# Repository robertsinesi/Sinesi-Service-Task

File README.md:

# KLM SRAM Expansion — Service Task

Belle II KLM service work · Instrumentation Development Lab, University of Hawai'i at Mānoa

## Overview

The KLM scintillator readout currently shares a single SRAM between the Bus A and
Bus B firmware modules through the SCROD FPGA. During multi-strip hits, pedestal
fetching becomes the rate-limiting step in waveform processing. This project adds
a second SRAM on an auxiliary daughtercard so each bus has its own memory path,
along with the power-distribution hardware needed to supply it.

Three boards make up the system:

| Board | Function |
| --- | --- |
| **Aux SRAM daughtercard** | Mounts to the spare 80-pin mezzanine connector on the scintillator motherboard; carries the second SRAM and a local 3.3 V regulator |
| **RTM +5 V board** | Rear transition module; taps +5 V from the crate backplane, fuses it, and feeds the wiring harness |
| **2-pole fanout board** | Splits the 12 AWG trunk into 22 AWG drops, one per SRAM card |

**Board design credit:** all three boards were designed by Chris Ketter (UH Mānoa),
with contributions from Horacio Ledesma. My role is prototype testing and design
finalization.

## Scope of this qualification task

Testing and validation:

- Test the prototype SRAM expansion board on the UH KLM testbench
- Test the associated RTM and power-distribution boards
- Verify electrical connections and power delivery across the full chain
- Confirm correct operation with the dedicated SRAM firmware

Finalization:

- Feed prototype results back into the board designs
- Help finalize assembly procedures ahead of the production run

Current files are in `Finalized-Boards/`. The SRAM card comes in three versions that share one outline and connector layout:

| Folder | Version |
| --- | --- |
| `KLM_aux_SRAM` | Standard card |
| `KLM_aux_SRAM_resistor` | Adds a 1 ohm current-sense resistor (R3) and two wire pads, so the supply current can be read with a meter (1 mV = 1 mA) |
| `KLM_aux_SRAM_INA226` | Standard card plus a 1 ohm current-sense resistor (R3, no wire pads) and an INA226 current monitor, read over I2C on spare lines 0 and 2 |

Editions of the boards are kept as git tags instead of folders. Each tag is the date of the edition followed by a short description:

| Tag | Edition |
| --- | --- |
| `2026-08-28-before-first-review` | Boards before the first design review |
| `2026-09-16-first-review-applied` | First review and its follow-up applied |
| `2026-09-17-polyswitch-1.1A` | Second review applied, with the lab-stock 1.1 A polyswitches |
| `2026-09-22-version-2` | Third review applied, polyswitches sized to the load; the boards built in October 2026 |
| `2026-10-20-old-board-folders` | Last commit that still had the `Old_Boards_Moved_<M-D-YY>/` folders, including the original boards as received |
| `2026-11-16-version-3` | Hand-soldering revision: longer pads, re-spaced wire pads and fuses, fanout mounting hole, three SRAM versions (current) |

To see an edition, pick its tag in the branch menu on GitHub and browse or download the files.

## Deliverable

- Finalized board designs
- Production of the boards
- Installation of the boards

## After the qualification task

Continued contribution to board production, testing, and installation as part of
ongoing KLM service work.

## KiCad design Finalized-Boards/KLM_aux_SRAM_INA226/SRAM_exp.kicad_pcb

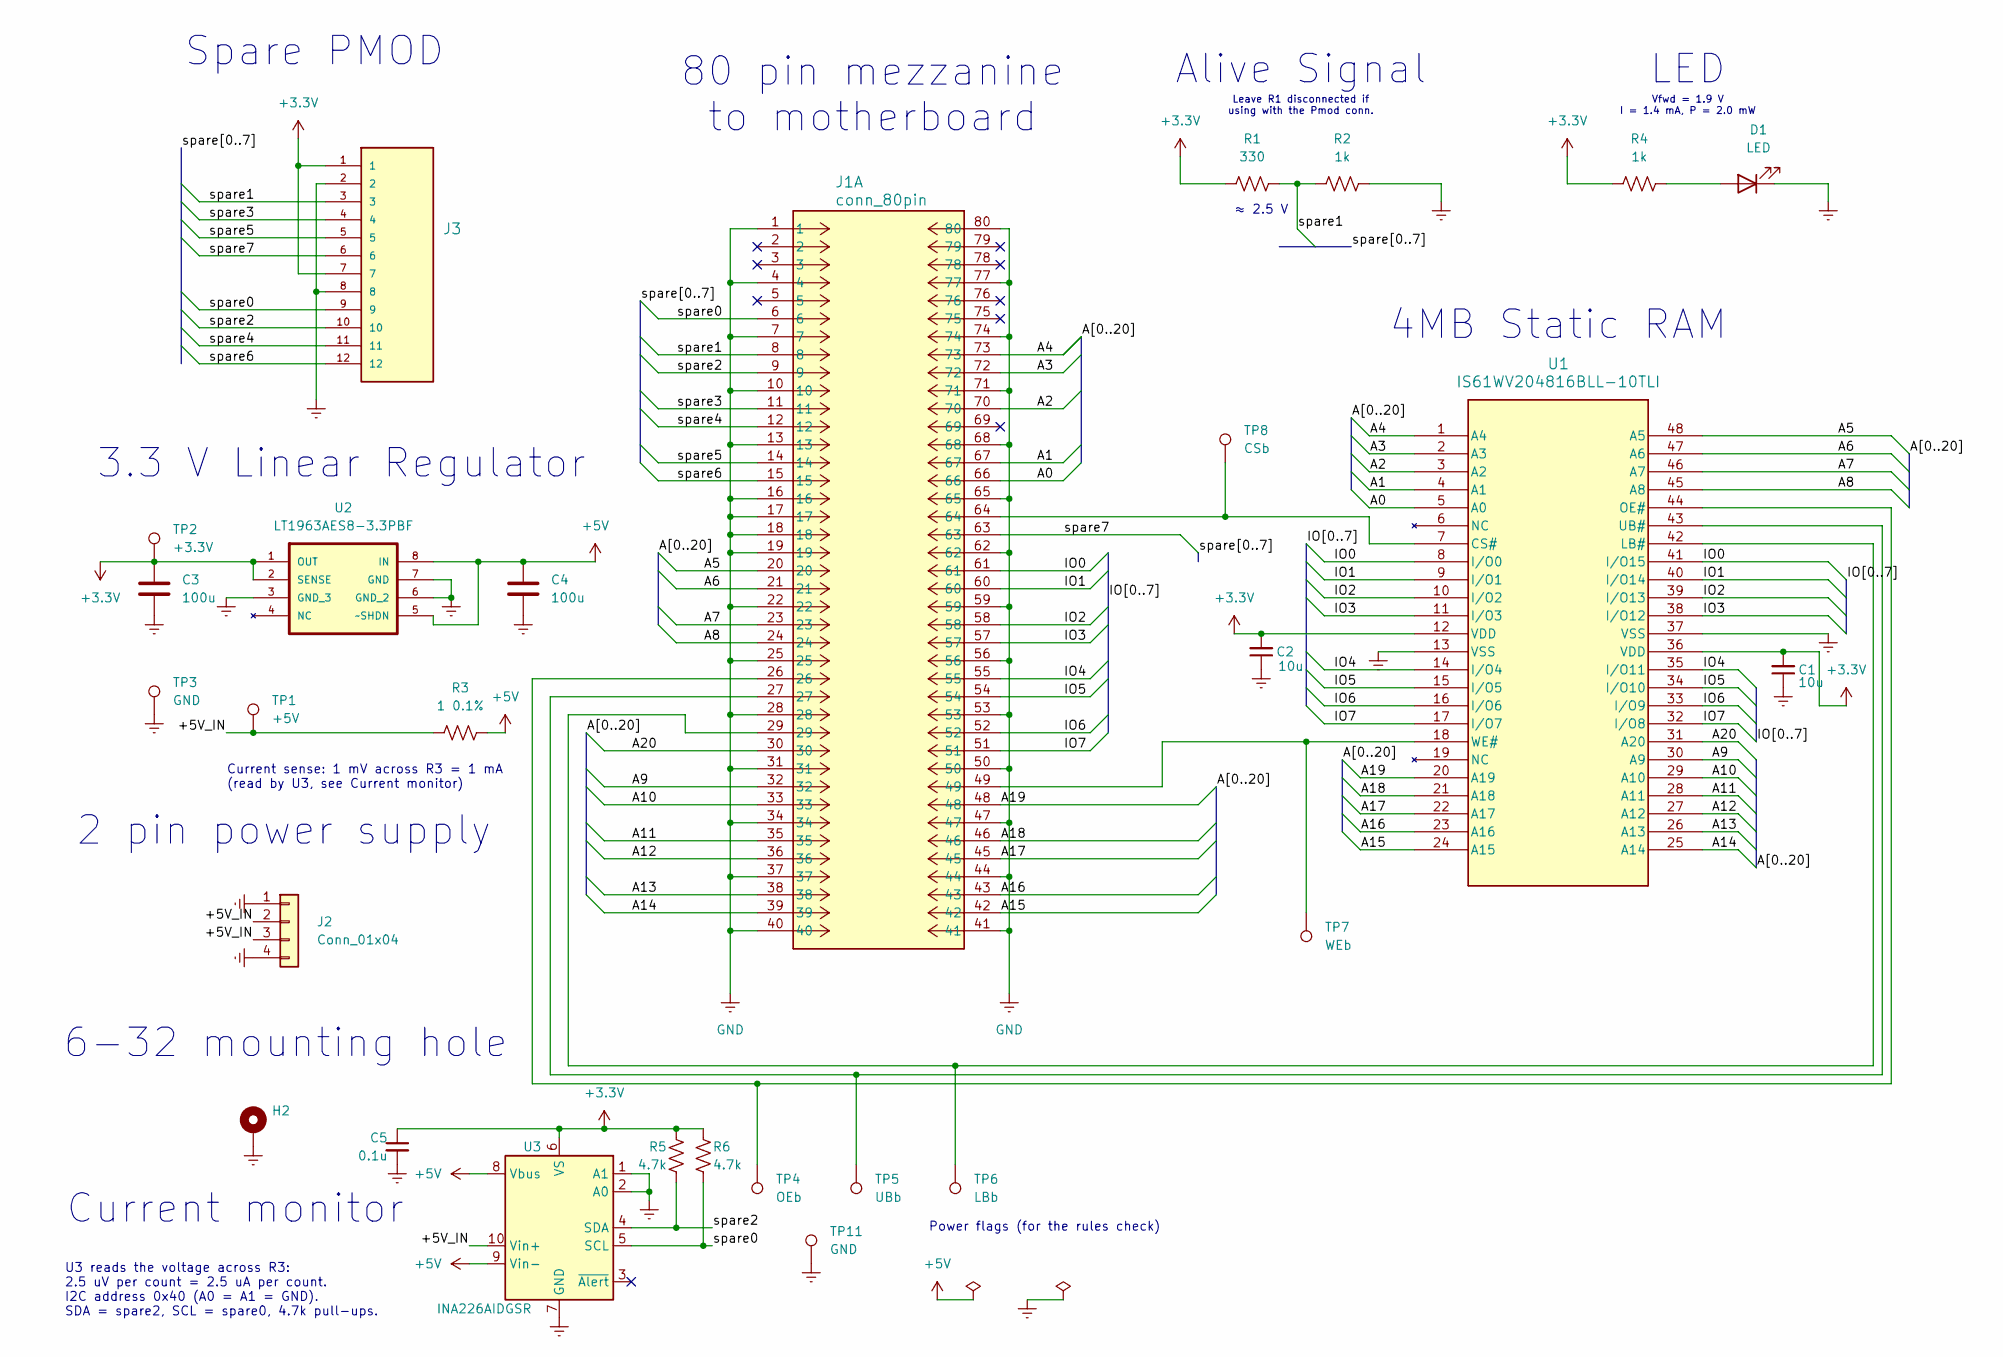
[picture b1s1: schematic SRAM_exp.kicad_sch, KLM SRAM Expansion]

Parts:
C1, C2: 10u; C_0603_1608Metric_Pad1.08x0.95mm_HandSolder
C3, C4: 100u; C_1206_3216Metric_Pad1.33x1.80mm_HandSolder
C5: 0.1u; C_0603_1608Metric_Pad1.08x0.95mm_HandSolder
D1: LED; LED_0402_1005Metric_Pad0.77x0.64mm_HandSolder
H2: MountingHole_Pad_Via_6-32_free_fit
J1: conn_80pin; CONN_5177985-3_TYC
J2: Conn_01x04; Molex_01x04_RA_22-05-3041
J3: Pmod_conn; CONN_HEADER_VERT_12POS_2.54MM; PARTREV R
R1: 330; R_0603_1608Metric_Pad0.98x0.95mm_HandSolder
R2, R4: 1k; R_0603_1608Metric_Pad0.98x0.95mm_HandSolder
R3: 1 0.1%; R_0805_2012Metric_Pad1.20x1.40mm_HandSolder
R5, R6: 4.7k; R_0603_1608Metric_Pad0.98x0.95mm_HandSolder
TP1: +5V; PinHeader_1x01_P1.00mm_Vertical
TP2: +3.3V; PinHeader_1x01_P1.00mm_Vertical
TP3, TP11: GND; PinHeader_1x01_P1.00mm_Vertical
TP4: OEb; TestPoint_THTPad_1.0x1.0mm_Drill0.5mm
TP5: UBb; TestPoint_THTPad_1.0x1.0mm_Drill0.5mm
TP6: LBb; TestPoint_THTPad_1.0x1.0mm_Drill0.5mm
TP7: WEb; TestPoint_THTPad_1.0x1.0mm_Drill0.5mm
TP8: CSb; TestPoint_THTPad_1.0x1.0mm_Drill0.5mm
U1: IS61WV204816BLL-10TLI; 48L_TSOP-1_12X20_ISI
U2: LT1963AES8-3.3PBF; SOIC127P600X175-8N; MPN LT1963AES8-3.3#PBF
U3: INA226AIDGSR; VSSOP-10_3x3mm_P0.5mm_HandSolder

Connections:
+3.3V: C1.2, C2.2, C3.1, C5.1, J3.1, J3.7, R1.1, R4.1, R5.1, R6.1, TP2.1 (1_1), U1.12 (VDD), U1.36 (VDD), U2.1 (OUT), U2.2 (SENSE), U3.6 (VS)
+5V: C4.1, R3.2, U2.5 (~SHDN), U2.8 (IN), U3.8 (Vbus), U3.9 (Vin-)
/+5V_IN: J2.2, J2.3, R3.1, TP1.1 (1_1), U3.10 (Vin+)
/A0: J1.66, U1.5 (A0)
/A1: J1.67, U1.4 (A1)
/A2: J1.70, U1.3 (A2)
/A3: J1.72, U1.2 (A3)
/A4: J1.73, U1.1 (A4)
/A5: J1.20, U1.48 (A5)
/A6: J1.21, U1.47 (A6)
/A7: J1.23, U1.46 (A7)
/A8: J1.24, U1.45 (A8)
/A9: J1.32, U1.30 (A9)
/A10: J1.33, U1.29 (A10)
/A11: J1.35, U1.28 (A11)
/A12: J1.36, U1.27 (A12)
/A13: J1.38, U1.26 (A13)
/A14: J1.39, U1.25 (A14)
/A15: J1.42, U1.24 (A15)
/A16: J1.43, U1.23 (A16)
/A17: J1.45, U1.22 (A17)
/A18: J1.46, U1.21 (A18)
/A19: J1.48, U1.20 (A19)
/A20: J1.30, U1.31 (A20)
/IO0: J1.61, U1.8 (I/O0), U1.41 (I/O15)
/IO1: J1.60, U1.9 (I/O1), U1.40 (I/O14)
/IO2: J1.58, U1.10 (I/O2), U1.39 (I/O13)
/IO3: J1.57, U1.11 (I/O3), U1.38 (I/O12)
/IO4: J1.55, U1.14 (I/O4), U1.35 (I/O11)
/IO5: J1.54, U1.15 (I/O5), U1.34 (I/O10)
/IO6: J1.52, U1.16 (I/O6), U1.33 (I/O9)
/IO7: J1.51, U1.17 (I/O7), U1.32 (I/O8)
/spare0: J1.6, J3.9, R6.2, U3.5 (SCL)
/spare1: J1.8, J3.3, R1.2, R2.1
/spare2: J1.9, J3.10, R5.2, U3.4 (SDA)
/spare3: J1.11, J3.4
/spare4: J1.12, J3.11
/spare5: J1.14, J3.5
/spare6: J1.15, J3.12
/spare7: J1.63, J3.6
GND: C1.1, C2.1, C3.2, C4.2, C5.2, D1.1 (K), H2.1 (1_1), J1.1, J1.4, J1.7, J1.10, J1.13, J1.16, J1.17, J1.18, J1.19, J1.22, J1.25, J1.28, J1.31, J1.34, J1.37, J1.40, J1.41, J1.44, J1.47, J1.50, J1.53, J1.56, J1.59, J1.62, J1.65, J1.68, J1.71, J1.74, J1.77, J1.80, J2.1, J2.4, J3.2, J3.8, R2.2, TP3.1 (1_1), TP11.1 (1_1), U1.13 (VSS), U1.37 (VSS), U2.3 (GND_3), U2.6 (GND_2), U2.7 (GND), U3.1 (A1), U3.2 (A0), U3.7 (GND)
unnamed: D1.2 (A), R4.2
unnamed: J1.64, TP8.1 (1_1), U1.7 (CS#)
unnamed: J1.29, TP6.1 (1_1), U1.42 (LB#)
unnamed: J1.26, TP4.1 (1_1), U1.44 (OE#)
unnamed: J1.27, TP5.1 (1_1), U1.43 (UB#)
unnamed: J1.49, TP7.1 (1_1), U1.18 (WE#)

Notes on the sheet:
Leave R1 disconnected if using with the Pmod conn.
Alive Signal
3.3 V Linear Regulator
Spare PMOD
4MB Static RAM
≈ 2.5 V
Vfwd = 1.9 V I = 1.4 mA, P = 2.0 mW
80 pin mezzanine to motherboard
2 pin power supply
6-32 mounting hole
LED
Power flags (for the rules check)
Current monitor
U3 reads the voltage across R3: 2.5 uV per count = 2.5 uA per count. I2C address 0x40 (A0 = A1 = GND). SDA = spare2, SCL = spare0, 4.7k pull-ups.
Current sense: 1 mV across R3 = 1 mA (read by U3, see Current monitor)

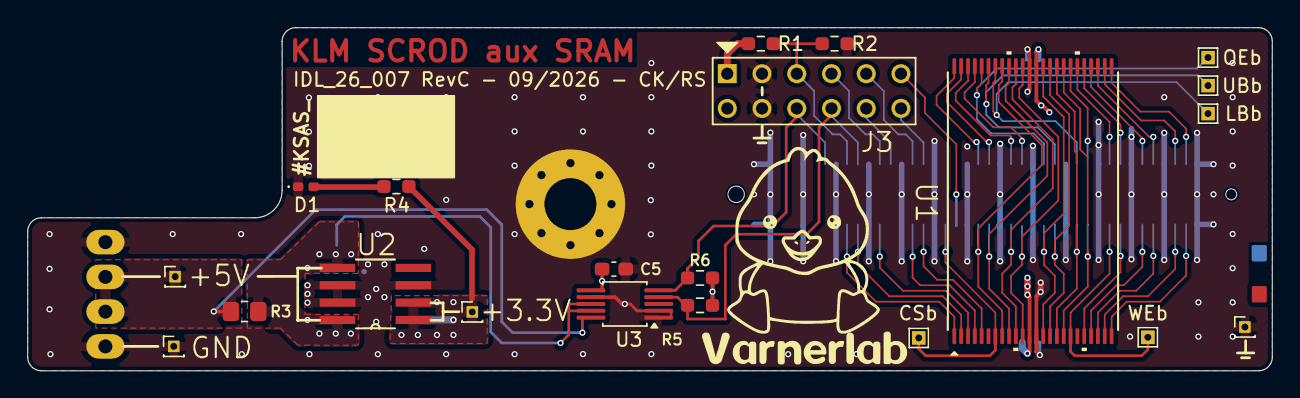
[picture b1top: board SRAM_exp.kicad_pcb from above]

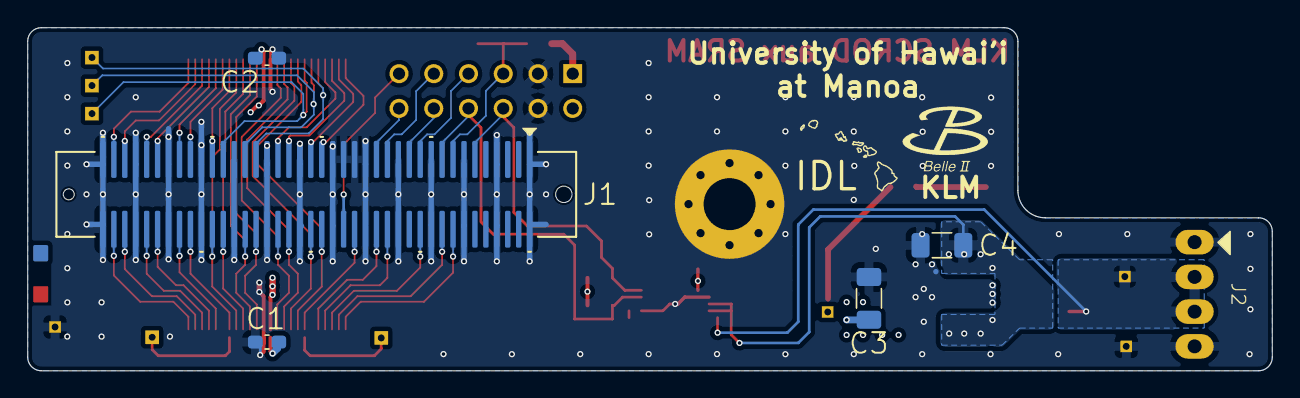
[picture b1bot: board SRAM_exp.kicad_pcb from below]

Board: 4 copper layers, 91.0 x 25.1 mm, 28 parts (6 on the bottom side), 47 nets.

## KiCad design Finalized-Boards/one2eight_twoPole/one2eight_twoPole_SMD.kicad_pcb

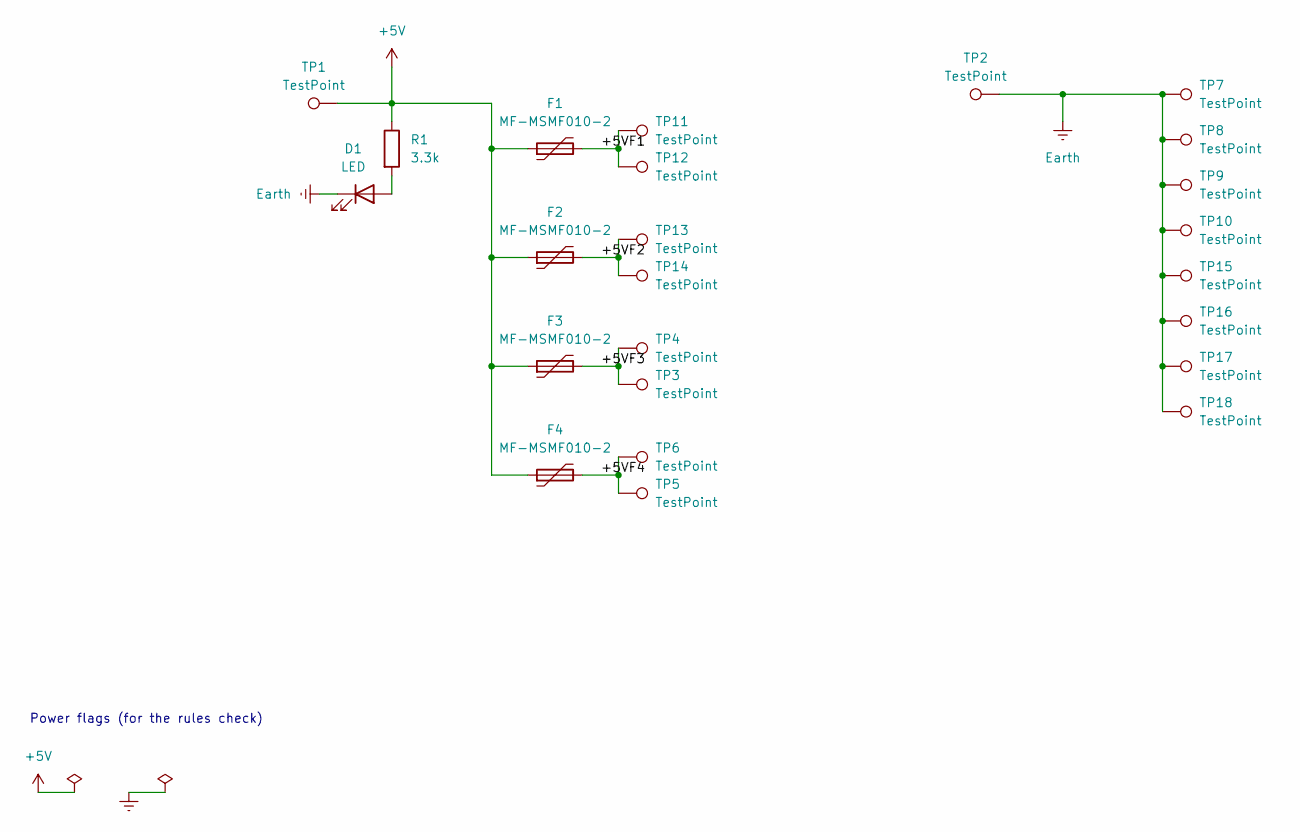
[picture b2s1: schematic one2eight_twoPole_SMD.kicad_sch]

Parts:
D1: LED; LED_0402_1005Metric_Pad0.77x0.64mm_HandSolder
F1, F2, F3, F4: MF-MSMF010-2; Fuse_1812_4532Metric_HandSolder_long
R1: 3.3k; R_0603_1608Metric_Pad0.98x0.95mm_HandSolder
TP1, TP2: TestPoint; PTH_12AWG
TP3, TP4, TP5, TP6, TP7, TP8, TP9, TP10, TP11, TP12, TP13, TP14, TP15, TP16, TP17, TP18: TestPoint; SolderWire-0.5sqmm_1x01_D0.9mm_OD2.1mm_Relief_3mm_shorter_v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

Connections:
+5V: F1.1, F2.1, F3.1, F4.1, R1.1, TP1.1 (1_1)
/+5VF1: F1.2, TP11.1 (1_1), TP12.1 (1_1)
/+5VF2: F2.2, TP13.1 (1_1), TP14.1 (1_1)
/+5VF3: F3.2, TP3.1 (1_1), TP4.1 (1_1)
/+5VF4: F4.2, TP5.1 (1_1), TP6.1 (1_1)
Earth: D1.1 (K), TP2.1 (1_1), TP7.1 (1_1), TP8.1 (1_1), TP9.1 (1_1), TP10.1 (1_1), TP15.1 (1_1), TP16.1 (1_1), TP17.1 (1_1), TP18.1 (1_1)
unnamed: D1.2 (A), R1.2

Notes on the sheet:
Power flags (for the rules check)

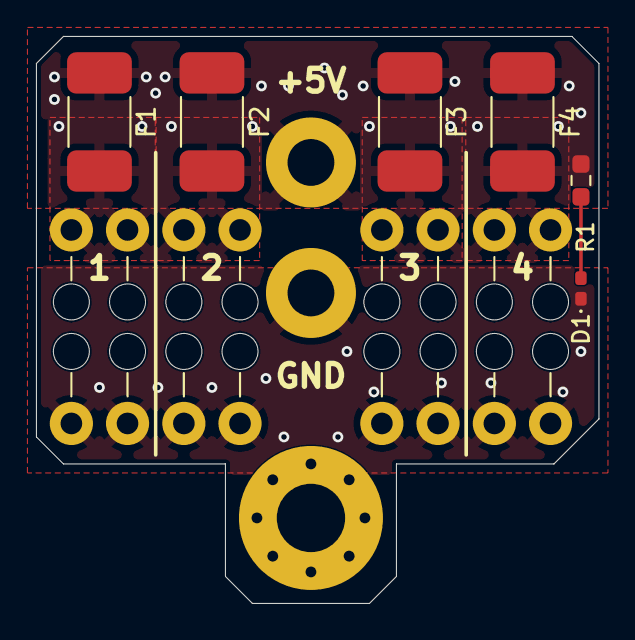
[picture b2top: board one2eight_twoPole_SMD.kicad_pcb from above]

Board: 4 copper layers, 31.2 x 31.5 mm, 25 parts (0 on the bottom side), 7 nets.

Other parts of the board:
H1: 6-32 mounting hole; MountingHole_Pad_Via_6-32_free_fit

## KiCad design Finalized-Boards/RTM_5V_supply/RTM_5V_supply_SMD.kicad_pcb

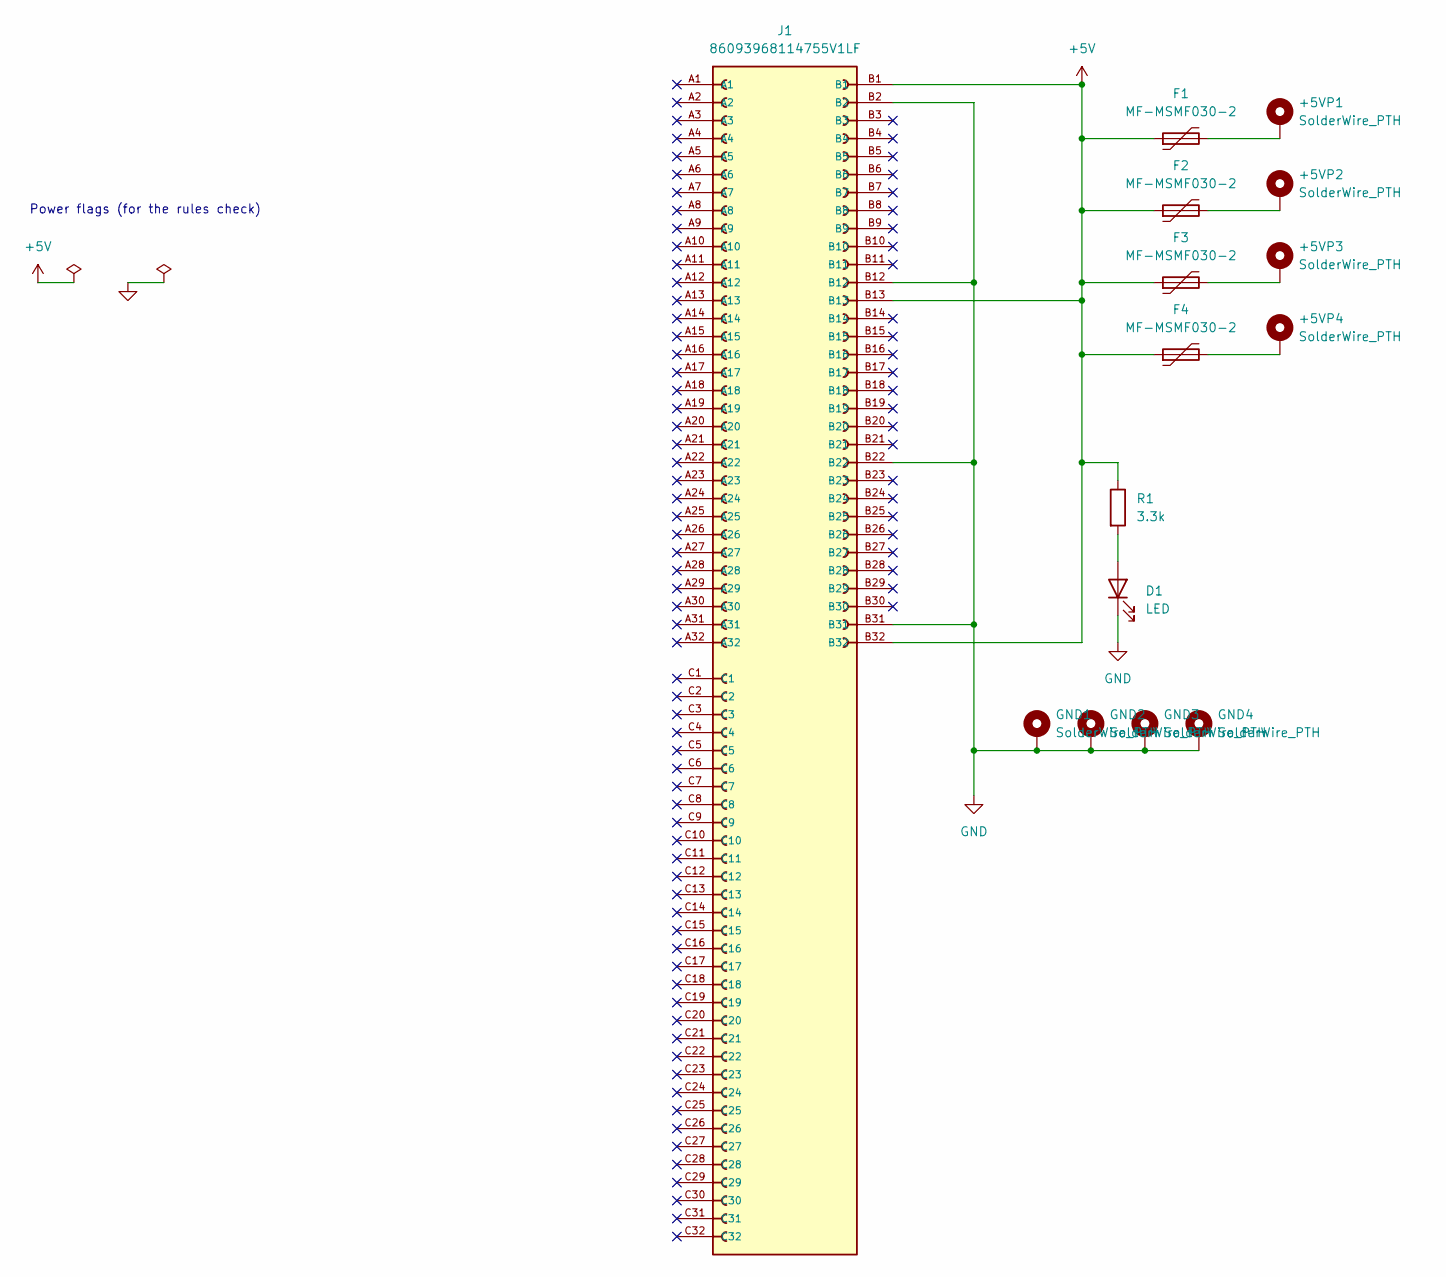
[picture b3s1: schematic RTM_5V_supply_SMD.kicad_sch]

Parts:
+5VP1, +5VP2, +5VP3, +5VP4: SolderWire_PTH; PTH_12AWG
D1: LED; LED_0402_1005Metric_Pad0.77x0.64mm_HandSolder
F1, F2, F3, F4: MF-MSMF030-2; Fuse_1812_4532Metric_HandSolder_long
GND1, GND2, GND3, GND4: SolderWire_PTH; PTH_12AWG
J1: 86093968114755V1LF; AMPHENOL_86093968114755V1LF; PARTREV F
R1: 3.3k; R_0603_1608Metric_Pad0.98x0.95mm_HandSolder

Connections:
+5V: F1.1, F2.1, F3.1, F4.1, J1.B1, J1.B13, J1.B32, R1.1
GND: D1.1 (K), GND1.1 (1_1), GND2.1 (1_1), GND3.1 (1_1), GND4.1 (1_1), J1.B2, J1.B12, J1.B22, J1.B31
unnamed: +5VP1.1 (1_1), F1.2
unnamed: +5VP2.1 (1_1), F2.2
unnamed: +5VP3.1 (1_1), F3.2
unnamed: +5VP4.1 (1_1), F4.2
unnamed: D1.2 (A), R1.2

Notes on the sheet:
Power flags (for the rules check)

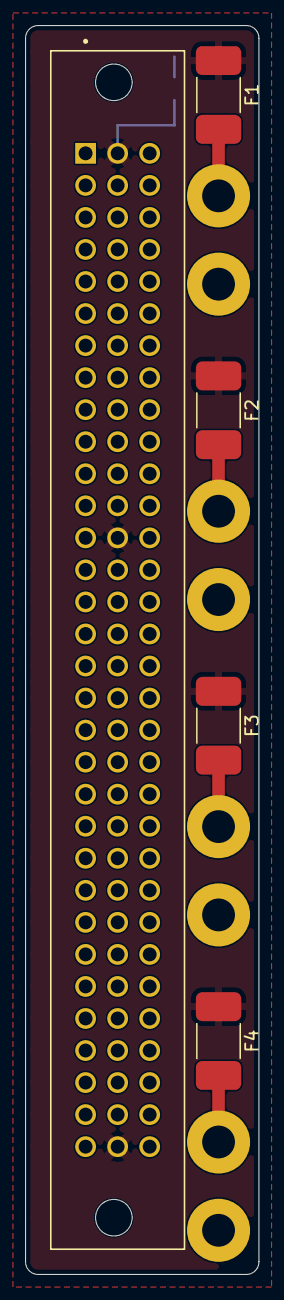
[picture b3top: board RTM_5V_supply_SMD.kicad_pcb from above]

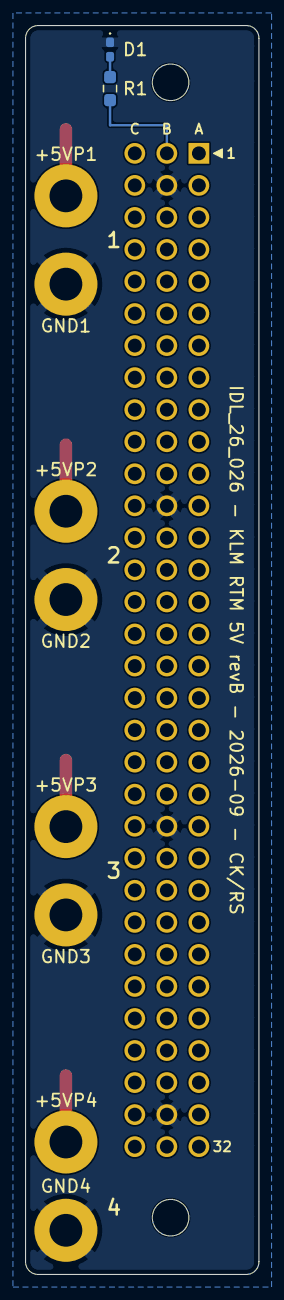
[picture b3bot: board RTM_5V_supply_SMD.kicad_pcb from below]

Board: 4 copper layers, 18.5 x 99.0 mm, 15 parts (10 on the bottom side), 7 nets.

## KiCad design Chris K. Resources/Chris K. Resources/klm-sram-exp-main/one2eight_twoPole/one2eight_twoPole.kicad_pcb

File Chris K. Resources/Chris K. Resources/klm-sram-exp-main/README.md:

# KLM SRAM Exp

## KLM SRAM Upgrade project
We are using a spare 80-pin connector on the motherboard to double the amount and bandwidth of SRAM available to our FPGA.

## Firmware
The new firmware for this project has been created in the main SCROD FW repository under the branch feature/SRAM_upgrade.

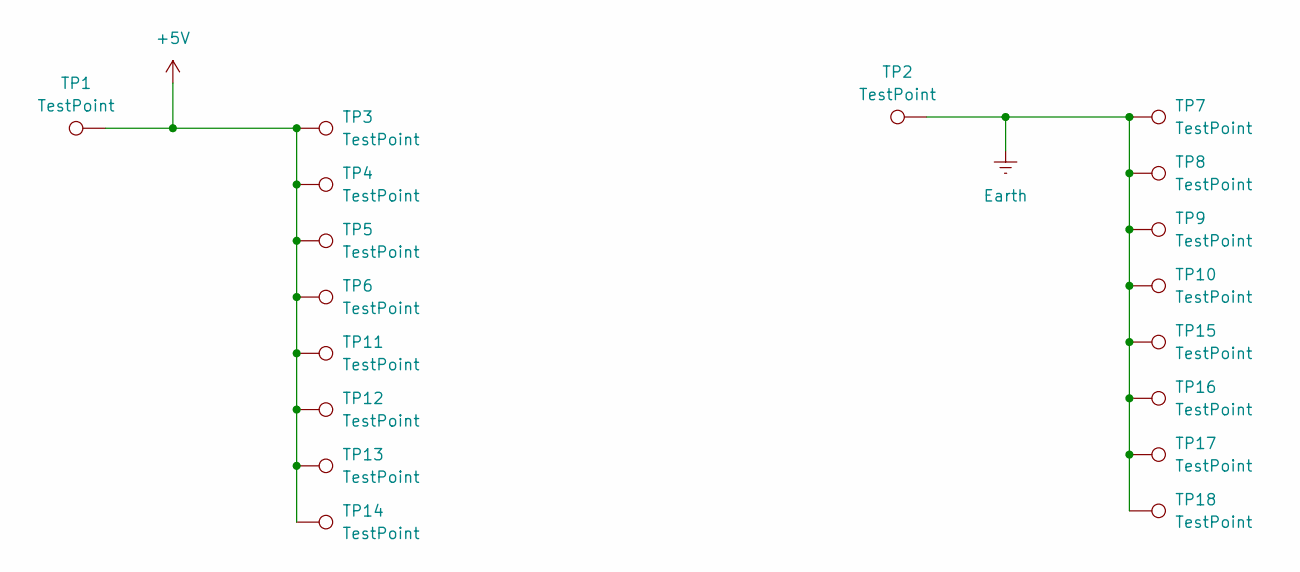
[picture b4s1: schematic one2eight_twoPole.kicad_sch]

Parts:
TP1, TP2: TestPoint; SolderWire-4sqmm_1x01_D3mm_OD6mm_Relief
TP3, TP4, TP5, TP6, TP7, TP8, TP9, TP10, TP11, TP12, TP13, TP14, TP15, TP16, TP17, TP18: TestPoint; SolderWire-0.5sqmm_1x01_D0.9mm_OD2.1mm_Relief

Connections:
+5V: TP1.1, TP3.1, TP4.1, TP5.1, TP6.1, TP11.1, TP12.1, TP13.1, TP14.1
Earth: TP2.1, TP7.1, TP8.1, TP9.1, TP10.1, TP15.1, TP16.1, TP17.1, TP18.1

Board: 4 copper layers, 18 parts (0 on the bottom side), 2 nets, no tracks yet.
